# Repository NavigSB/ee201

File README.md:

# Electrical Engineering 201
This is Gavin Bullock's git repository for the UW EE 201 class. Each different branch is a different
lab. This main branch is not associated with a lab.

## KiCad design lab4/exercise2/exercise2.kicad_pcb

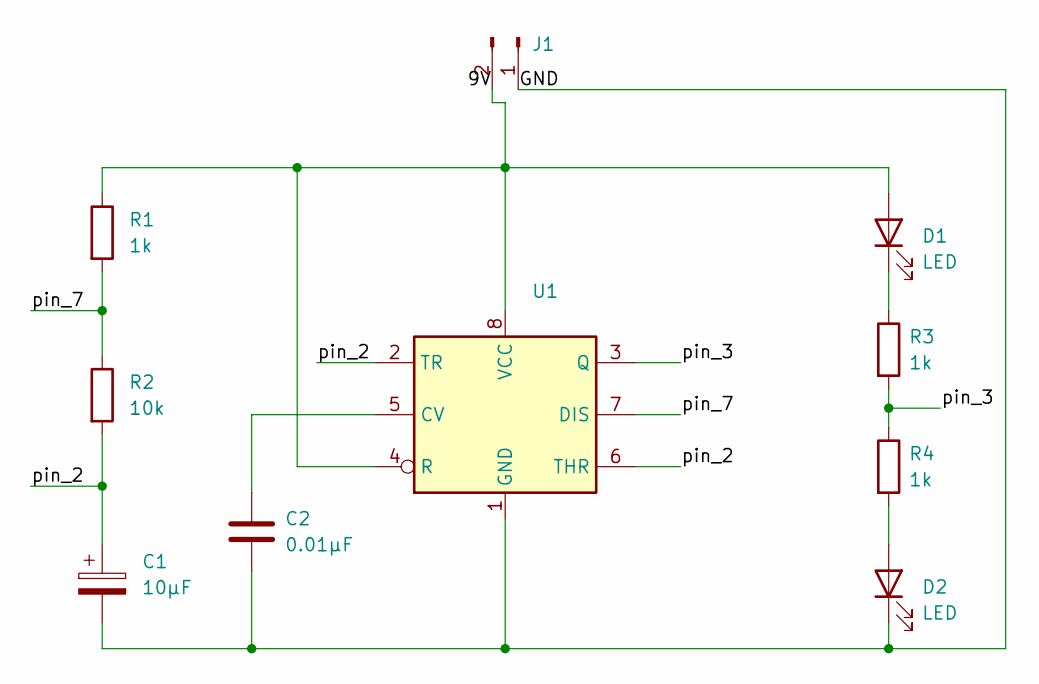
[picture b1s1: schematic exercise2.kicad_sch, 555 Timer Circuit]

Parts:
C1: 10μF; CP_EIA-3216-18_Kemet-A_Pad1.58x1.35mm_HandSolder
C2: 0.01μF; C_0805_2012Metric_Pad1.18x1.45mm_HandSolder
D1, D2: LED; LED_1206_3216Metric_Pad1.42x1.75mm_HandSolder
J1: Conn_01x02_Male; TerminalBlock_bornier-2_P5.08mm
R1, R3, R4: 1k; R_0805_2012Metric_Pad1.20x1.40mm_HandSolder
R2: 10k; R_0805_2012Metric_Pad1.20x1.40mm_HandSolder
U1: NE555D; SOIC-8-1EP_3.9x4.9mm_P1.27mm_EP2.29x3mm

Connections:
/9V: D1.2 (A), J1.2, R1.1, U1.4 (R), U1.8 (VCC)
/GND: C1.2, C2.2, D2.1 (K), J1.1, U1.1 (GND)
/pin_2: C1.1, R2.2, U1.2 (TR), U1.6 (THR)
/pin_3: R3.2, R4.1, U1.3 (Q)
/pin_7: R1.2, R2.1, U1.7 (DIS)
unnamed: C2.1, U1.5 (CV)
unnamed: D1.1 (K), R3.1
unnamed: D2.2 (A), R4.2

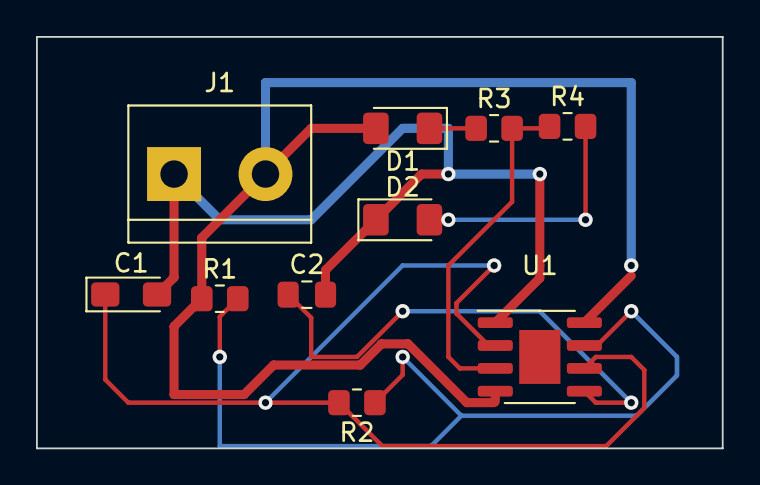
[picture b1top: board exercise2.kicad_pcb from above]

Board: 2 copper layers, 38.1 x 22.9 mm, 10 parts (0 on the bottom side), 8 nets.

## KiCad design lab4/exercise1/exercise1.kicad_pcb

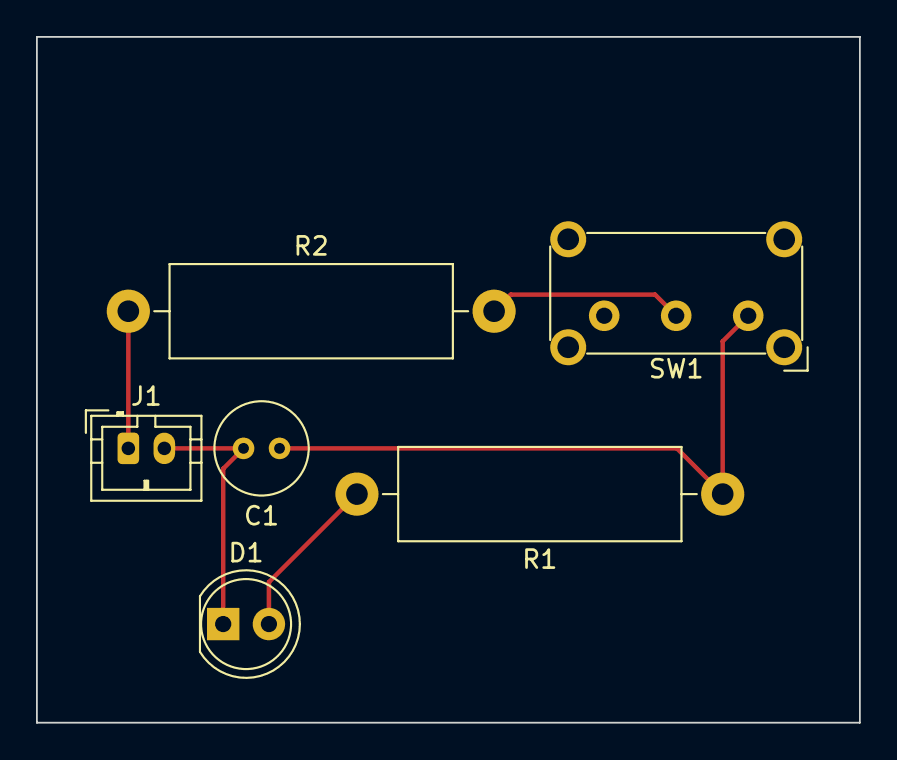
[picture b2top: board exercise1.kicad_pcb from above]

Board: 2 copper layers, 45.7 x 38.1 mm, 6 parts (0 on the bottom side), 5 nets.

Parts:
C1: 4.7 μF; C_Radial_D5.0mm_H5.0mm_P2.00mm
D1: LED; LED_D5.0mm
J1: 9 V; JST_PH_B2B-PH-K_1x02_P2.00mm_Vertical
R1: 20 kΩ; R_Axial_DIN0516_L15.5mm_D5.0mm_P20.32mm_Horizontal
R2: 2.2 kΩ; R_Axial_DIN0516_L15.5mm_D5.0mm_P20.32mm_Horizontal
SW1: SW_SPDT; SW_E-Switch_EG1224_SPDT_Angled

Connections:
unnamed: C1.1, R1.1, SW1.1 (A)
unnamed: C1.2, D1.1 (K), J1.2
unnamed: D1.2 (A), R1.2
unnamed: J1.1, R2.1
unnamed: R2.2, SW1.2 (B)

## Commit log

2023-01-13 Added aboutMe folder and made markdown page
2023-01-13 Add some nice formatting :)
2023-01-20 Exercise 1 prelim
2023-01-20 Added exercise 2
2023-01-20 Got exercise 3 working
2023-01-20 Exercise 4 prelim
2023-01-20 Finished exercise 4
2023-01-20 Moved exercise 4 into Arduino folder
2023-01-27 Completed exercise 1
2023-01-27 Better gitignore
2023-01-27 Completed exercise 2
2023-01-27 Fixed labeling mistake
2023-02-03 Added soldering pictures
2023-02-10 Added PCB layouts
2023-02-17 Made power traces 20 mils
2023-02-17 Generated gerber and drill files
